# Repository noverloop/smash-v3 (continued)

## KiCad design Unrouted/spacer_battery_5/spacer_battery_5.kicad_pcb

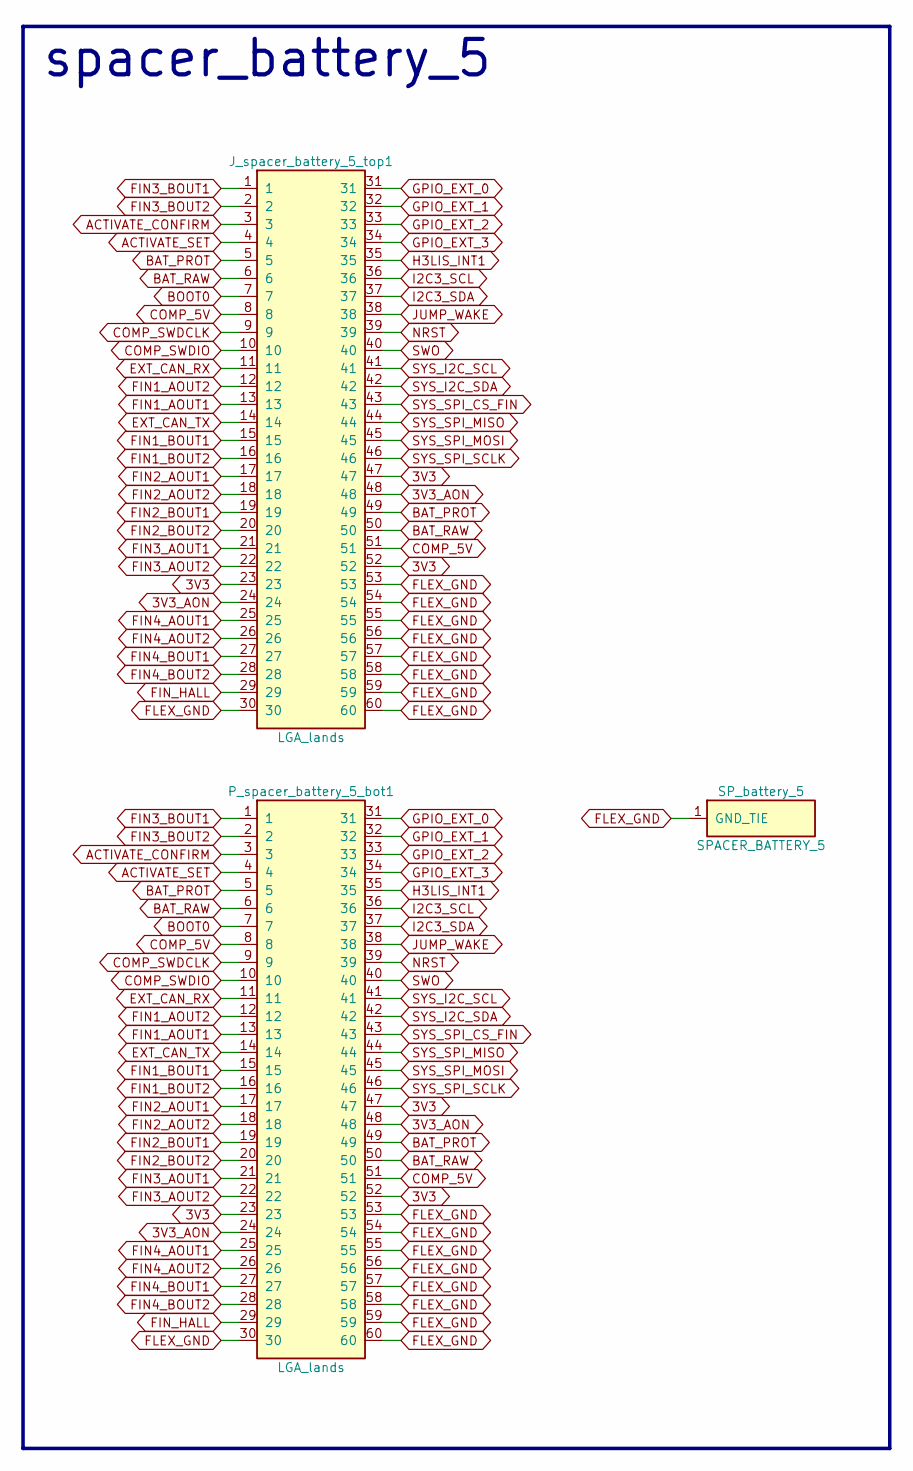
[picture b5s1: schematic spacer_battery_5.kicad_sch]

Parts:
J_spacer_battery_5_top1: LGA_lands; J_spacer_battery_5_top; MPN LGA_lands
P_spacer_battery_5_bot1: LGA_lands; P_spacer_battery_5_bot; MPN LGA_lands
SP_battery_5: SPACER_BATTERY_5; Spacer_Mechanical_34mm

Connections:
3V3: J_spacer_battery_5_top1.23, J_spacer_battery_5_top1.47, J_spacer_battery_5_top1.52, P_spacer_battery_5_bot1.23, P_spacer_battery_5_bot1.47, P_spacer_battery_5_bot1.52
3V3_AON: J_spacer_battery_5_top1.24, J_spacer_battery_5_top1.48, P_spacer_battery_5_bot1.24, P_spacer_battery_5_bot1.48
ACTIVATE_CONFIRM: J_spacer_battery_5_top1.3, P_spacer_battery_5_bot1.3
ACTIVATE_SET: J_spacer_battery_5_top1.4, P_spacer_battery_5_bot1.4
BAT_PROT: J_spacer_battery_5_top1.5, J_spacer_battery_5_top1.49, P_spacer_battery_5_bot1.5, P_spacer_battery_5_bot1.49
BAT_RAW: J_spacer_battery_5_top1.6, J_spacer_battery_5_top1.50, P_spacer_battery_5_bot1.6, P_spacer_battery_5_bot1.50
BOOT0: J_spacer_battery_5_top1.7, P_spacer_battery_5_bot1.7
COMP_5V: J_spacer_battery_5_top1.8, J_spacer_battery_5_top1.51, P_spacer_battery_5_bot1.8, P_spacer_battery_5_bot1.51
COMP_SWDCLK: J_spacer_battery_5_top1.9, P_spacer_battery_5_bot1.9
COMP_SWDIO: J_spacer_battery_5_top1.10, P_spacer_battery_5_bot1.10
EXT_CAN_RX: J_spacer_battery_5_top1.11, P_spacer_battery_5_bot1.11
EXT_CAN_TX: J_spacer_battery_5_top1.14, P_spacer_battery_5_bot1.14
FIN1_AOUT1: J_spacer_battery_5_top1.13, P_spacer_battery_5_bot1.13
FIN1_AOUT2: J_spacer_battery_5_top1.12, P_spacer_battery_5_bot1.12
FIN1_BOUT1: J_spacer_battery_5_top1.15, P_spacer_battery_5_bot1.15
FIN1_BOUT2: J_spacer_battery_5_top1.16, P_spacer_battery_5_bot1.16
FIN2_AOUT1: J_spacer_battery_5_top1.17, P_spacer_battery_5_bot1.17
FIN2_AOUT2: J_spacer_battery_5_top1.18, P_spacer_battery_5_bot1.18
FIN2_BOUT1: J_spacer_battery_5_top1.19, P_spacer_battery_5_bot1.19
FIN2_BOUT2: J_spacer_battery_5_top1.20, P_spacer_battery_5_bot1.20
FIN3_AOUT1: J_spacer_battery_5_top1.21, P_spacer_battery_5_bot1.21
FIN3_AOUT2: J_spacer_battery_5_top1.22, P_spacer_battery_5_bot1.22
FIN3_BOUT1: J_spacer_battery_5_top1.1, P_spacer_battery_5_bot1.1
FIN3_BOUT2: J_spacer_battery_5_top1.2, P_spacer_battery_5_bot1.2
FIN4_AOUT1: J_spacer_battery_5_top1.25, P_spacer_battery_5_bot1.25
FIN4_AOUT2: J_spacer_battery_5_top1.26, P_spacer_battery_5_bot1.26
FIN4_BOUT1: J_spacer_battery_5_top1.27, P_spacer_battery_5_bot1.27
FIN4_BOUT2: J_spacer_battery_5_top1.28, P_spacer_battery_5_bot1.28
FIN_HALL: J_spacer_battery_5_top1.29, P_spacer_battery_5_bot1.29
FLEX_GND: J_spacer_battery_5_top1.30, J_spacer_battery_5_top1.53, J_spacer_battery_5_top1.54, J_spacer_battery_5_top1.55, J_spacer_battery_5_top1.56, J_spacer_battery_5_top1.57, J_spacer_battery_5_top1.58, J_spacer_battery_5_top1.59, J_spacer_battery_5_top1.60, P_spacer_battery_5_bot1.30, P_spacer_battery_5_bot1.53, P_spacer_battery_5_bot1.54, P_spacer_battery_5_bot1.55, P_spacer_battery_5_bot1.56, P_spacer_battery_5_bot1.57, P_spacer_battery_5_bot1.58, P_spacer_battery_5_bot1.59, P_spacer_battery_5_bot1.60, SP_battery_5.1
GPIO_EXT_0: J_spacer_battery_5_top1.31, P_spacer_battery_5_bot1.31
GPIO_EXT_1: J_spacer_battery_5_top1.32, P_spacer_battery_5_bot1.32
GPIO_EXT_2: J_spacer_battery_5_top1.33, P_spacer_battery_5_bot1.33
GPIO_EXT_3: J_spacer_battery_5_top1.34, P_spacer_battery_5_bot1.34
H3LIS_INT1: J_spacer_battery_5_top1.35, P_spacer_battery_5_bot1.35
I2C3_SCL: J_spacer_battery_5_top1.36, P_spacer_battery_5_bot1.36
I2C3_SDA: J_spacer_battery_5_top1.37, P_spacer_battery_5_bot1.37
JUMP_WAKE: J_spacer_battery_5_top1.38, P_spacer_battery_5_bot1.38
NRST: J_spacer_battery_5_top1.39, P_spacer_battery_5_bot1.39
SWO: J_spacer_battery_5_top1.40, P_spacer_battery_5_bot1.40
SYS_I2C_SCL: J_spacer_battery_5_top1.41, P_spacer_battery_5_bot1.41
SYS_I2C_SDA: J_spacer_battery_5_top1.42, P_spacer_battery_5_bot1.42
SYS_SPI_CS_FIN: J_spacer_battery_5_top1.43, P_spacer_battery_5_bot1.43
SYS_SPI_MISO: J_spacer_battery_5_top1.44, P_spacer_battery_5_bot1.44
SYS_SPI_MOSI: J_spacer_battery_5_top1.45, P_spacer_battery_5_bot1.45
SYS_SPI_SCLK: J_spacer_battery_5_top1.46, P_spacer_battery_5_bot1.46

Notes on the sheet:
spacer_battery_5

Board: 2 copper layers, 4 parts (1 on the bottom side), 46 nets, no tracks yet.

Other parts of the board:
MH1: smash_mech_potting

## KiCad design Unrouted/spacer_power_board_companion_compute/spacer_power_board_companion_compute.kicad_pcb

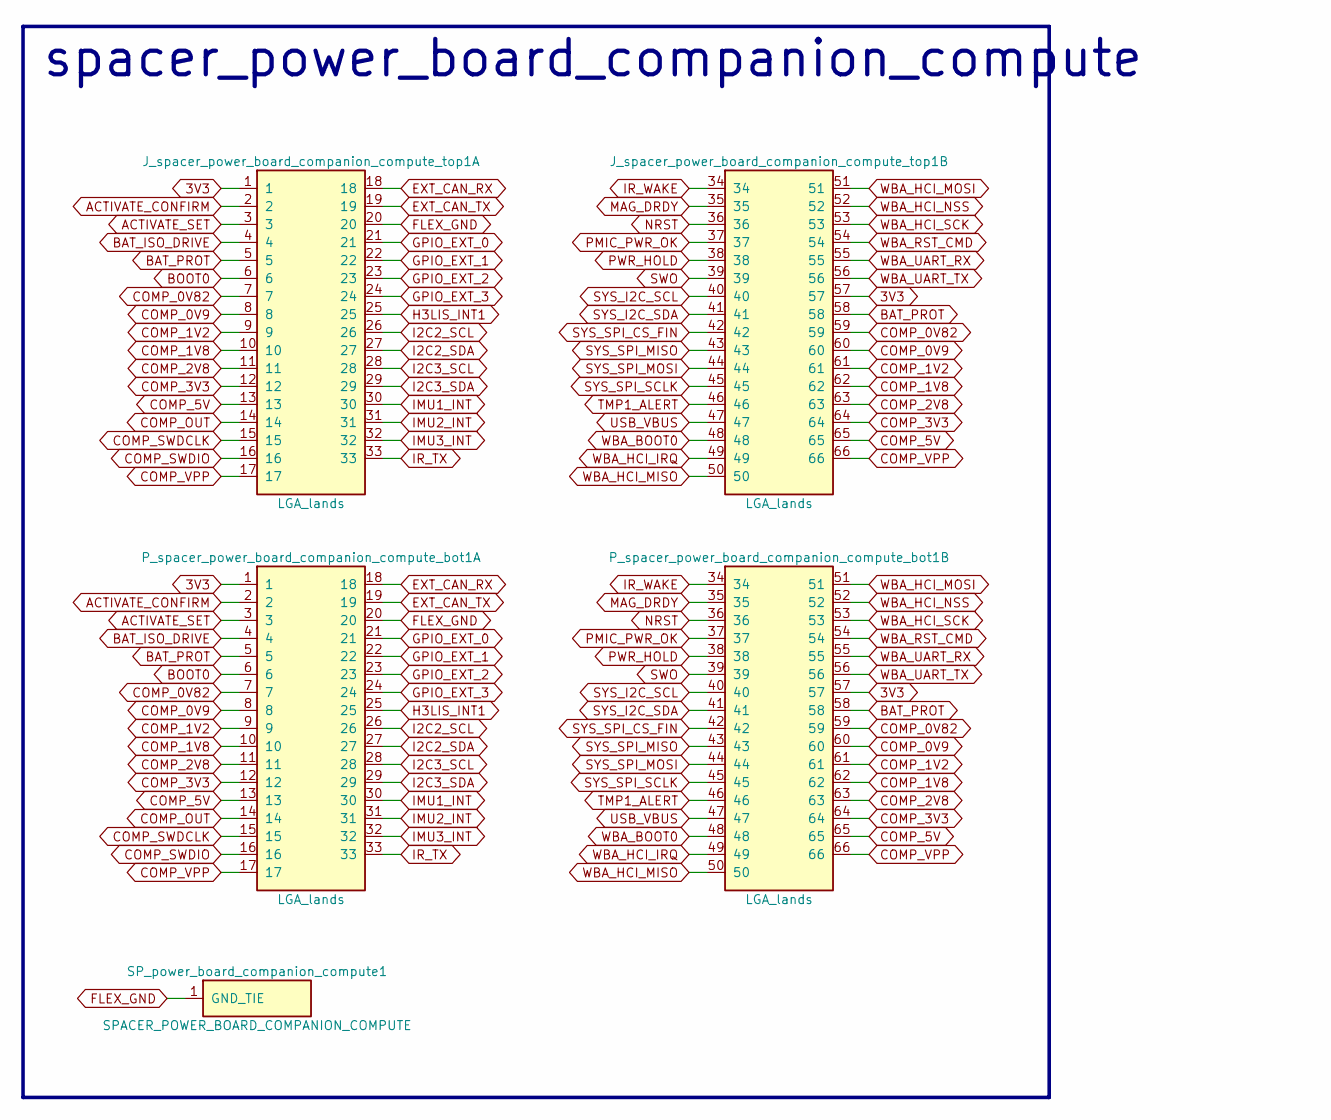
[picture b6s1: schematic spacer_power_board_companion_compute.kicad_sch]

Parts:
J_spacer_power_board_companion_compute_top1: LGA_lands; J_spacer_power_board_companion_compute_top; MPN LGA_lands
P_spacer_power_board_companion_compute_bot1: LGA_lands; P_spacer_power_board_companion_compute_bot; MPN LGA_lands
SP_power_board_companion_compute1: SPACER_POWER_BOARD_COMPANION_COMPUTE; Spacer_Mechanical_34mm

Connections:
3V3: J_spacer_power_board_companion_compute_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.1, J_spacer_power_board_companion_compute_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.57, P_spacer_power_board_companion_compute_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.1, P_spacer_power_board_companion_compute_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.57
ACTIVATE_CONFIRM: J_spacer_power_board_companion_compute_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.2, P_spacer_power_board_companion_compute_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.2
ACTIVATE_SET: J_spacer_power_board_companion_compute_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.3, P_spacer_power_board_companion_compute_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.3
BAT_ISO_DRIVE: J_spacer_power_board_companion_compute_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.4, P_spacer_power_board_companion_compute_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.4
BAT_PROT: J_spacer_power_board_companion_compute_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.5, J_spacer_power_board_companion_compute_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.58, P_spacer_power_board_companion_compute_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.5, P_spacer_power_board_companion_compute_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.58
BOOT0: J_spacer_power_board_companion_compute_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.6, P_spacer_power_board_companion_compute_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.6
COMP_0V9: J_spacer_power_board_companion_compute_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.8, J_spacer_power_board_companion_compute_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.60, P_spacer_power_board_companion_compute_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.8, P_spacer_power_board_companion_compute_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.60
COMP_0V82: J_spacer_power_board_companion_compute_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.7, J_spacer_power_board_companion_compute_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.59, P_spacer_power_board_companion_compute_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.7, P_spacer_power_board_companion_compute_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.59
COMP_1V2: J_spacer_power_board_companion_compute_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.9, J_spacer_power_board_companion_compute_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.61, P_spacer_power_board_companion_compute_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.9, P_spacer_power_board_companion_compute_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.61
COMP_1V8: J_spacer_power_board_companion_compute_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.10, J_spacer_power_board_companion_compute_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.62, P_spacer_power_board_companion_compute_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.10, P_spacer_power_board_companion_compute_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.62
COMP_2V8: J_spacer_power_board_companion_compute_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.11, J_spacer_power_board_companion_compute_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.63, P_spacer_power_board_companion_compute_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.11, P_spacer_power_board_companion_compute_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.63
COMP_3V3: J_spacer_power_board_companion_compute_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.12, J_spacer_power_board_companion_compute_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.64, P_spacer_power_board_companion_compute_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.12, P_spacer_power_board_companion_compute_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.64
COMP_5V: J_spacer_power_board_companion_compute_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.13, J_spacer_power_board_companion_compute_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.65, P_spacer_power_board_companion_compute_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.13, P_spacer_power_board_companion_compute_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.65
COMP_OUT: J_spacer_power_board_companion_compute_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.14, P_spacer_power_board_companion_compute_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.14
COMP_SWDCLK: J_spacer_power_board_companion_compute_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.15, P_spacer_power_board_companion_compute_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.15
COMP_SWDIO: J_spacer_power_board_companion_compute_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.16, P_spacer_power_board_companion_compute_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.16
COMP_VPP: J_spacer_power_board_companion_compute_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.17, J_spacer_power_board_companion_compute_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.66, P_spacer_power_board_companion_compute_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.17, P_spacer_power_board_companion_compute_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.66
EXT_CAN_RX: J_spacer_power_board_companion_compute_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.18, P_spacer_power_board_companion_compute_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.18
EXT_CAN_TX: J_spacer_power_board_companion_compute_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.19, P_spacer_power_board_companion_compute_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.19
FLEX_GND: J_spacer_power_board_companion_compute_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.20, P_spacer_power_board_companion_compute_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.20, SP_power_board_companion_compute1.1
GPIO_EXT_0: J_spacer_power_board_companion_compute_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.21, P_spacer_power_board_companion_compute_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.21
GPIO_EXT_1: J_spacer_power_board_companion_compute_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.22, P_spacer_power_board_companion_compute_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.22
GPIO_EXT_2: J_spacer_power_board_companion_compute_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.23, P_spacer_power_board_companion_compute_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.23
GPIO_EXT_3: J_spacer_power_board_companion_compute_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.24, P_spacer_power_board_companion_compute_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.24
H3LIS_INT1: J_spacer_power_board_companion_compute_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.25, P_spacer_power_board_companion_compute_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.25
I2C2_SCL: J_spacer_power_board_companion_compute_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.26, P_spacer_power_board_companion_compute_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.26
I2C2_SDA: J_spacer_power_board_companion_compute_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.27, P_spacer_power_board_companion_compute_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.27
I2C3_SCL: J_spacer_power_board_companion_compute_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.28, P_spacer_power_board_companion_compute_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.28
I2C3_SDA: J_spacer_power_board_companion_compute_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.29, P_spacer_power_board_companion_compute_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.29
IMU1_INT: J_spacer_power_board_companion_compute_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.30, P_spacer_power_board_companion_compute_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.30
IMU2_INT: J_spacer_power_board_companion_compute_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.31, P_spacer_power_board_companion_compute_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.31
IMU3_INT: J_spacer_power_board_companion_compute_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.32, P_spacer_power_board_companion_compute_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.32
IR_TX: J_spacer_power_board_companion_compute_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.33, P_spacer_power_board_companion_compute_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.33
IR_WAKE: J_spacer_power_board_companion_compute_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.34, P_spacer_power_board_companion_compute_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.34
MAG_DRDY: J_spacer_power_board_companion_compute_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.35, P_spacer_power_board_companion_compute_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.35
NRST: J_spacer_power_board_companion_compute_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.36, P_spacer_power_board_companion_compute_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.36
PMIC_PWR_OK: J_spacer_power_board_companion_compute_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.37, P_spacer_power_board_companion_compute_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.37
PWR_HOLD: J_spacer_power_board_companion_compute_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.38, P_spacer_power_board_companion_compute_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.38
SWO: J_spacer_power_board_companion_compute_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.39, P_spacer_power_board_companion_compute_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.39
SYS_I2C_SCL: J_spacer_power_board_companion_compute_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.40, P_spacer_power_board_companion_compute_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.40
SYS_I2C_SDA: J_spacer_power_board_companion_compute_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.41, P_spacer_power_board_companion_compute_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.41
SYS_SPI_CS_FIN: J_spacer_power_board_companion_compute_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.42, P_spacer_power_board_companion_compute_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.42
SYS_SPI_MISO: J_spacer_power_board_companion_compute_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.43, P_spacer_power_board_companion_compute_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.43
SYS_SPI_MOSI: J_spacer_power_board_companion_compute_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.44, P_spacer_power_board_companion_compute_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.44
SYS_SPI_SCLK: J_spacer_power_board_companion_compute_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.45, P_spacer_power_board_companion_compute_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.45
TMP1_ALERT: J_spacer_power_board_companion_compute_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.46, P_spacer_power_board_companion_compute_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.46
USB_VBUS: J_spacer_power_board_companion_compute_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.47, P_spacer_power_board_companion_compute_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.47
WBA_BOOT0: J_spacer_power_board_companion_compute_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.48, P_spacer_power_board_companion_compute_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.48
WBA_HCI_IRQ: J_spacer_power_board_companion_compute_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.49, P_spacer_power_board_companion_compute_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.49
WBA_HCI_MISO: J_spacer_power_board_companion_compute_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.50, P_spacer_power_board_companion_compute_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.50
WBA_HCI_MOSI: J_spacer_power_board_companion_compute_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.51, P_spacer_power_board_companion_compute_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.51
WBA_HCI_NSS: J_spacer_power_board_companion_compute_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.52, P_spacer_power_board_companion_compute_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.52
WBA_HCI_SCK: J_spacer_power_board_companion_compute_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.53, P_spacer_power_board_companion_compute_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.53
WBA_RST_CMD: J_spacer_power_board_companion_compute_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.54, P_spacer_power_board_companion_compute_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.54
WBA_UART_RX: J_spacer_power_board_companion_compute_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.55, P_spacer_power_board_companion_compute_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.55
WBA_UART_TX: J_spacer_power_board_companion_compute_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.56, P_spacer_power_board_companion_compute_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.56

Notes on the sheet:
spacer_power_board_companion_compute

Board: 2 copper layers, 5 parts (1 on the bottom side), 56 nets, no tracks yet.

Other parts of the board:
MH1, MH2: smash_mech_potting
